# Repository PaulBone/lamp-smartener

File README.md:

Lamp Smartener
===============

This is the "Lamp Smartener" or "Overengineered Light Switch" it works on
USB powered LED lights.

WIP

Component selection
-------------------

 * the NE7000 can be substituted for any N-type with a Vth around 1-2 V. and
   can switch 5V,
 * The AO3400 can be substituted for any N-type that can handle 600mA of
   current, and switch 5V.  And disipate 1.25W of heat.
 * Likewise AO3401 can be substituted for any P-type that can handle 600mA of
   current and switch 5V.
 * TODO resistor tollerance
 * TODO current limiter advice.

Assembly notes
--------------

Solder the small SMD components first, it's easier to reach them before you
put the big ones in.

Solder the switches before mounting the USB ports, the usb port shield pin
will interfere with switch soldering.

Do not confuse the mosfet types.  They're different for good reasons.
p-type and n-type just arnt' compatible.  However, the NE7000 can be
substituted with more AO3400 units (probably), but not the other way around.

TODO: Add alterantive 2 and 1 port versions with the current limiter.

Mount the uC with either pin headers or directly.  for direct soldering try
holding it in place with pins/wires in the through-holes then solder the
edges.

Firmware
--------

Firmware uses the esphome framework and can be compiled with, replace
lamp-smartener.yaml with the name of the .yaml file to match your lamp
smartener, single-lamp.yaml or double-lamp.yaml.  If you're using
single-lamp.yaml check the pin names in the file match what you've soldered
on the board.

   $ mkdir /tmp/esphome
   $ docker run --rm --privileged -v "${PWD}":/config -v "/tmp/esphome:/config/.esphome" --device=/dev/ttyACM0 -it ghcr.io/esphome/esphome run lamp-smartener.yaml

Assuming you have pluged the ESP32 module into your PC and it is connected
at /dev/ttyACM0

Alternatlvely you can build and flash it in separete steps, this will erase
any wifi credentials that may be on the device, the above method does not:

   $ mkdir /tmp/esphome
   $ docker run --rm --privileged -v "${PWD}":/config -v "/tmp/esphome:/config/.esphome" -it ghcr.io/esphome/esphome compile lamp-smartener.yaml
   $ cp /tmp/esphome/build/lamp-smartener/.pioenvs/lamp-smartener/firmware.factory.bin .
   $ esptool.py write_flash 0x0 firmware.factory.bin

The device will reboot and create a new Wifi network with "Lamp Smartener"
in its name.  The password is "Overengineered Light Switch".  Connect to it
with something like your phone then visit http://192.168.4.1  Tell the page
there what wifi network you'd like it to join.

Home assistant will be able to discover it, if you use (or would like to
use) esphome's dashboard to maintain firmware updates (which is available as
a HA addon) you can adopt the device there as well.

Using the device
----------------

Each button will twoggle it's lamp (if installed) or drive automations in
Home Assistant.  In the single lamp version by default the 2nd button does
nothing directly, but it can be used to run automations in home assistant.

Pressing and holding both buttons together for 10 seconds will initiate a
factory reset, the status light will glow orange and any lamps will flash,
keep holding the buttons for another 5s to conform the factory reset,
otherwise release buttons to cancel.

Each button can be "disconnected" from its light by turning the "direct"
control switch off for that switch and lamp.  Eg if the button should run a
home assistant automation instead (which may turn on the lamp to 50%
brightness if you touch the button after midnight, and full brightness
otherwise).  The "direct" setting will persisted across reboots.

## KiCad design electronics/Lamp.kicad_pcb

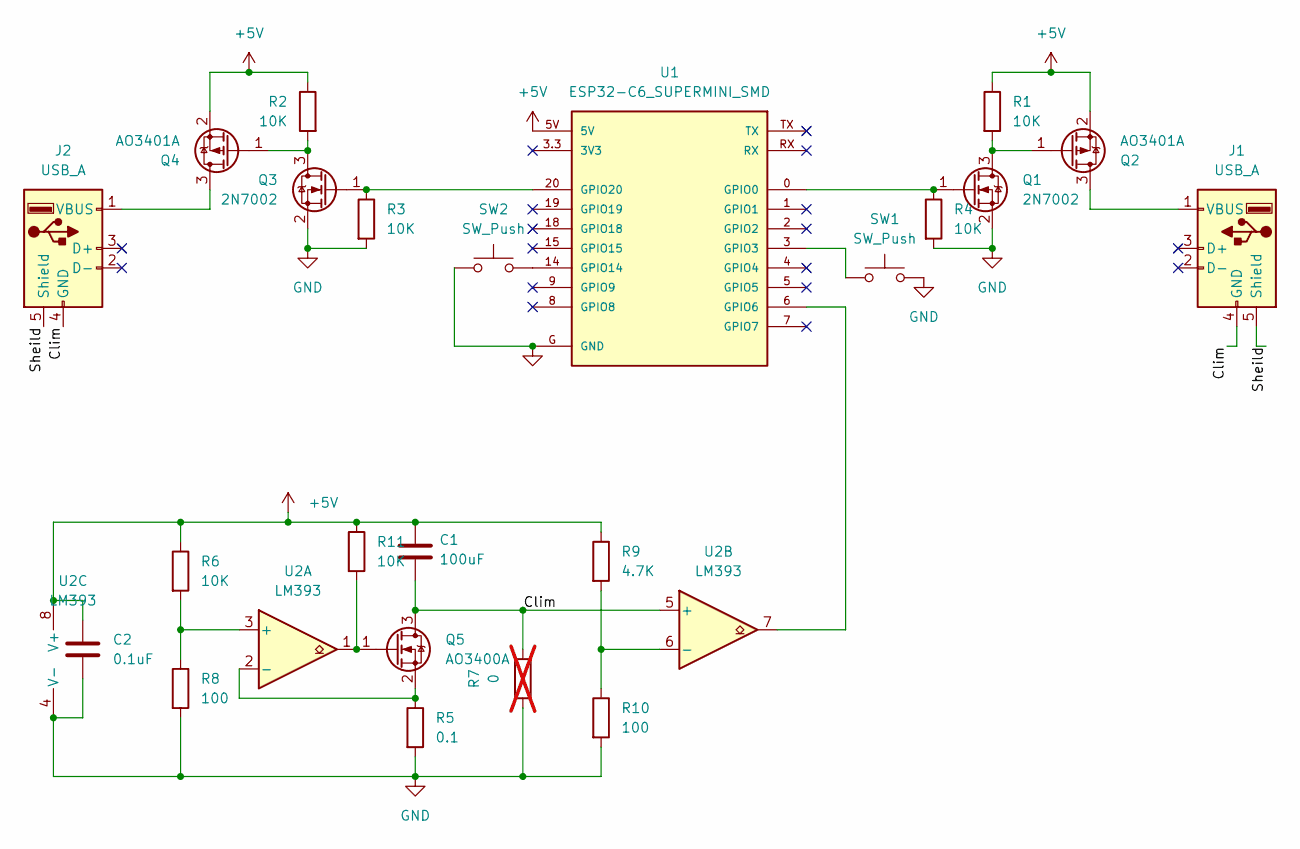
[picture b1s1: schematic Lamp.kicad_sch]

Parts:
C1: 100uF; CP_Elec_5x5.7
C2: 0.1uF; C_0805_2012Metric_Pad1.18x1.45mm_HandSolder
J1, J2: USB_A; USB_A_Receptacle_GCT_USB1046
Q1, Q3: 2N7002; SOT-23_Handsoldering
Q2, Q4: AO3401A; SOT-23_Handsoldering
Q5: AO3400A; SOT-23_Handsoldering
R1, R2, R3, R4, R6, R11: 10K; R_0805_2012Metric_Pad1.20x1.40mm_HandSolder
R5: 0.1; R_0805_2012Metric_Pad1.20x1.40mm_HandSolder
R7: 0; R_0805_2012Metric_Pad1.20x1.40mm_HandSolder; not fitted
R8, R10: 100; R_0805_2012Metric_Pad1.20x1.40mm_HandSolder
R9: 4.7K; R_0805_2012Metric_Pad1.20x1.40mm_HandSolder
SW1, SW2: SW_Push; SW_SMD_Tact_6mm
U1: ESP32-C6_SUPERMINI_SMD; MODULE_ESP32-C3_SUPERMINI
U2: LM393; SOP-8_3.9x4.9mm_P1.27mm

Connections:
+5V: C1.1, C2.1, Q2.2 (S), Q4.2 (S), R1.1, R2.1, R6.1, R9.1, R11.1, U1.5V, U2.8 (V+)
/Clim: C1.2, J1.4 (GND), J2.4 (GND), Q5.3 (D), R7.2, U2.5 (+)
/Sheild: J1.5 (Shield), J2.5 (Shield)
GND: C2.2, Q1.2 (S), Q3.2 (S), R3.2, R4.2, R5.2, R7.1, R8.2, R10.2, SW1.2, SW2.1, U1.G (GND), U2.4 (V-)
unnamed: J1.1 (VBUS), Q2.3 (D)
unnamed: J2.1 (VBUS), Q4.3 (D)
unnamed: Q1.3 (D), Q2.1 (G), R1.2
unnamed: Q1.1 (G), R4.1, U1.0 (GPIO0)
unnamed: Q3.3 (D), Q4.1 (G), R2.2
unnamed: Q3.1 (G), R3.1, U1.20 (GPIO20)
unnamed: Q5.1 (G), R11.2, U2.1
unnamed: Q5.2 (S), R5.1, U2.2 (-)
unnamed: SW1.1, U1.3 (GPIO3)
unnamed: U1.6 (GPIO6), U2.7
unnamed: SW2.2, U1.14 (GPIO14)
unnamed: R6.2, R8.1, U2.3 (+)
unnamed: R9.2, R10.1, U2.6 (-)

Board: 2 copper layers, 24 parts (8 on the bottom side), 17 nets, no tracks yet.

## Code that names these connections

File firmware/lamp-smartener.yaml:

substitutions:
  name: lamp-smartener
  friendly_name: "Lamp Smartener"

esphome:
  name: "${name}"
  friendly_name: "${friendly_name}"
  name_add_mac_suffix: True
  project:
    name: esphome.lamp_smartener
    version: "1.1"
  on_boot: 
    then:
      script.execute: update_status

esp32:
  board: esp32-c6-devkitm-1
  variant: ESP32C6
  framework:
    type: esp-idf

# Enable logging
logger:

# Enable Home Assistant API
api:

ota:
  - platform: esphome

# This points to the public location of this yaml file.
dashboard_import:
  package_import_url: github://PaulBone/lamp-smartener/firmware/lamp-smartener.yaml
  import_full_config: false # or true


wifi:
  # Enable fallback hotspot (captive portal) in case wifi connection fails
  # Not supported in zigbee configuration.
  ap:
    ssid: "Lamp-Smartener Fallback Hotspot"
    password: "Overengineered Light Switch"

  on_connect:
    - globals.set:
        id: wifi_connected
        value: 'true'
    - script.execute: update_status
  on_disconnect:
    - globals.set:
        id: wifi_connected
        value: 'false'
    - script.execute: update_status

# Not supported with zigbee   
captive_portal:

web_server:

script:
  id: update_status
  mode: restart
  then:
    - if:
        condition:
          api.connected:
        then:
          light.turn_on:
            id: status
            brightness: 1.0
            red: 0
            green: 0
            blue: 1
        else:
        - if:
            condition: 
              lambda: |-
                return id(wifi_connected);
            then:
              light.turn_on:
                id: status
                brightness: 1.0
                red: 0
                green: 1.0
                blue: 0
            else:
              light.turn_on:
                id: status
                brightness: 1.0
                red: 1.0
                green: 0
                blue: 0
    - delay: 60s
    - light.turn_off:
        id: status

globals:
  - id: wifi_connected
    type: bool
    initial_value: "false"
    restore_value: false
  - id: direct_1
    type: bool
    initial_value: "true"
    restore_value: false
  - id: direct_2
    type: bool
    initial_value: "true"
    restore_value: false

output:
  - platform: ledc
    id: pwm_light_1
    pin: GPIO0
  - platform: ledc
    id: pwm_light_2
    pin: GPIO20

light:
  - platform: esp32_rmt_led_strip
    id: status
    internal: true
    num_leds: 1
    pin: GPIO8
    rgb_order: GRB
    chipset: ws2812
    default_transition_length: 0s
  - platform: monochromatic
    output: pwm_light_1
    name: "Light"
    id: light_1
    effects:
      - pulse:
          name: Notification
          transition_length: 1.5s
          update_interval: 1.5s
          min_brightness: 10%
          max_brightness: 100%
      - pulse:
          name: Alert
          transition_length:
            on_length: 0s
            off_length: 0.5s
          update_interval: 0.4s
          min_brightness: 0%
          max_brightness: 100%
      - flicker:
          name: Flicker
          intensity: 2.5%
          alpha: 97.5%
  - platform: monochromatic
    output: pwm_light_2
    name: "Light 2"
    id: light_2
    # Disabled on this model.
    internal: True
    effects:
      - pulse:
          name: Notification
          transition_length: 1.5s
          update_interval: 1.5s
          min_brightness: 10%
          max_brightness: 100%
      - pulse:
          name: Alert
          transition_length:
            on_length: 0s
            off_length: 0.5s
          update_interval: 0.4s
          min_brightness: 0%
          max_brightness: 100%
      - flicker:
          name: Flicker
          intensity: 2.5%
          alpha: 97.5%

binary_sensor:
  - platform: gpio
    name: "Button 1"
    id: button_1
    pin:
      number: GPIO3
      mode:
        input: true
        pullup: true
      inverted: true
    on_click:
      then:
        - if:
            condition:
              - or:
                - lambda: return id(direct_1);
                - not:
                    api.connected: 
            then:
              - light.toggle: light_1
  - platform: gpio
    name: "Button 2"
    id: button_2
    on_click:
      then:
        - if:
            condition:
              - or:
                - lambda: return id(direct_2);
                - not:
                    api.connected: 
            then:
              - light.toggle: light_2
    pin:
      number: GPIO14
      mode:
        input: true
        pullup: true
      inverted: true

switch:
  - name: Direct Control
    icon: mdi:cog
    entity_category: CONFIG
    platform: template
    restore_mode: RESTORE_DEFAULT_ON
    lambda: return id(direct_1);
    turn_on_action:
      then:
        - globals.set:
            id: direct_1
            value: 'true'
    turn_off_action: 
      then:
        - globals.set: 
            id: direct_1
            value: 'false'
  - name: Direct Control 2
    icon: mdi:cog
    internal: true
    entity_category: CONFIG
    platform: template
    restore_mode: RESTORE_DEFAULT_ON
    lambda: return id(direct_2);
    turn_on_action:
      then:
        - globals.set:
            id: direct_2
            value: 'true'
    turn_off_action: 
      then:
        - globals.set: 
            id: direct_2
            value: 'false'

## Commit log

2025-06-09 Initial check-in
2025-06-09 Small updates
    * Add README and move some notes there
    * Rehane the notex.txt file
    * Add .gitignore file
2025-06-09 Move electronics designs into subdirectory
2025-06-09 Start adding firmware
2025-06-10 Remove numbers from switch 1 and direct 1 names
2025-06-12 Update PCB
2025-06-13 Rename config file and set lamp pin properly
2025-06-13 Add a factory reset option to the firmware.
2025-06-14 Add CAD file for first version
2025-06-14 Slimmer box for when board is mounted directly
2025-06-23 Finish the lamp box
2025-06-23 WIP the schematic
2025-06-23 Update schamatic
2026-02-24 Add double lamp configuration
2026-02-27 Remove global variables and seperate persistance.
2026-02-28 Commit CAD .step files
